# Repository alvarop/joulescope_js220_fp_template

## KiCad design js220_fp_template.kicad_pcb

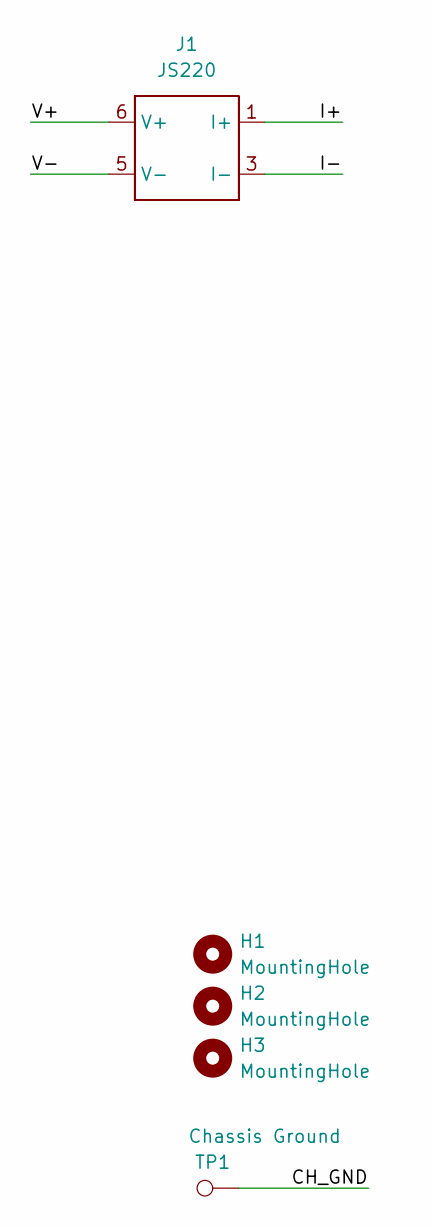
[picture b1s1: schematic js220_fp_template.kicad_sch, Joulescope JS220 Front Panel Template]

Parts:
H1, H2: MountingHole; MOUNTING_HOLE_3.5_W_KO
H3: MountingHole; MOUNTING_HOLE_3.3MM
J1: JS220; SAMTEC_TSM-103-01-S-DV-A
TP1: Chassis Ground; TINY_TP

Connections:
/CH_GND: TP1.1
/I+: J1.1 (I+), J1.2 (I+)
/I-: J1.3 (I-), J1.4 (I-)
/V+: J1.6 (V+)
/V-: J1.5 (V-)

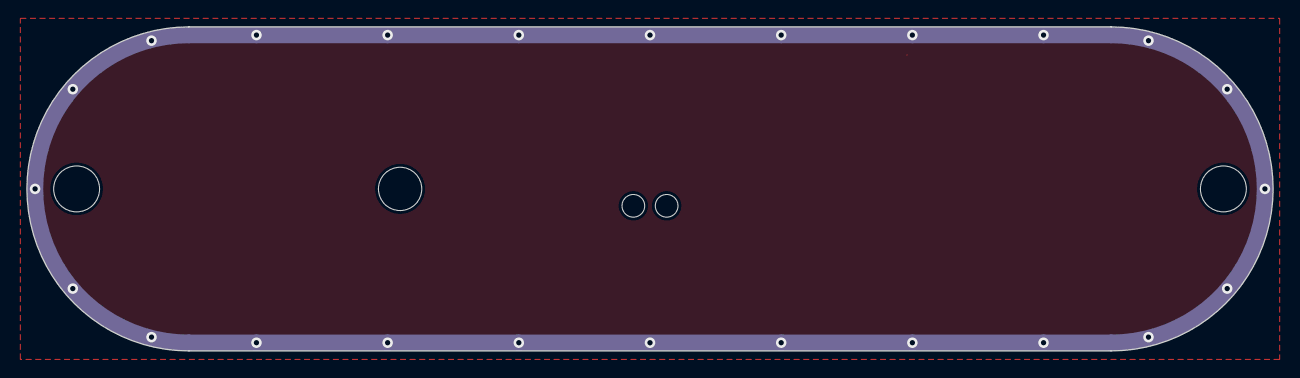
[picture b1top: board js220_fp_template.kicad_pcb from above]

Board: 2 copper layers, 95.0 x 24.7 mm, 5 parts (1 on the bottom side), 2 nets.

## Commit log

2022-11-12 Fixed flipped pinout with I+ I-
